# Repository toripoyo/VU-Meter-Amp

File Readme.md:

VU Meter Driver Amp

* -10dBv/+4dBm input level select
* 0 to -15dB 6step gain select
* Meter brightness adjust

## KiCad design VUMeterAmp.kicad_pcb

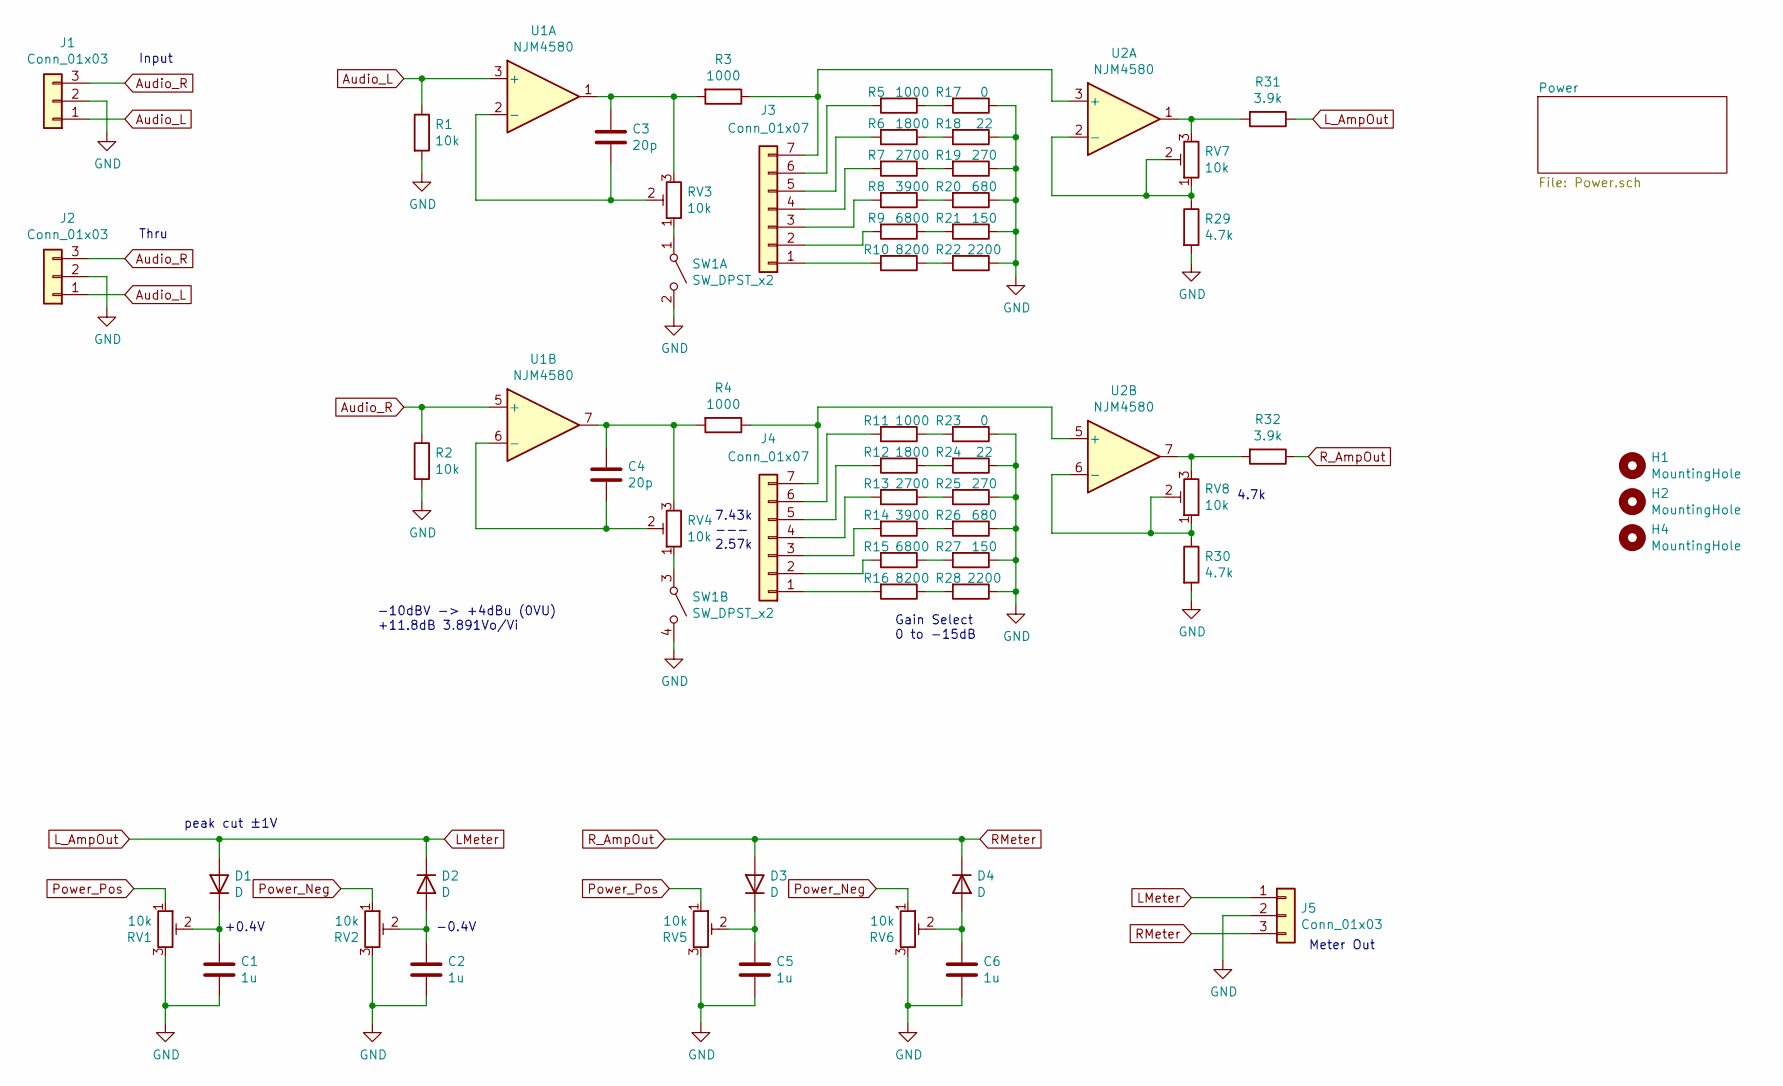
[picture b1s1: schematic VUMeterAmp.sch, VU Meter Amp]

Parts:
C1, C2, C5, C6: 1u; C_0603_1608Metric_Pad1.05x0.95mm_HandSolder
C3, C4: 20p; C_0603_1608Metric_Pad1.05x0.95mm_HandSolder
D1, D2, D3, D4: D; D_SOD-123F
H1, H2, H4: MountingHole; MountingHole_3.2mm_M3
J1, J2, J5: Conn_01x03; JST_XH_B3B-XH-A_1x03_P2.50mm_Vertical
J3, J4: Conn_01x07; JST_XH_B7B-XH-A_1x07_P2.50mm_Vertical
R1, R2: 10k; R_0603_1608Metric_Pad1.05x0.95mm_HandSolder
R3, R4, R5, R11: 1000; R_0603_1608Metric_Pad1.05x0.95mm_HandSolder
R6, R12: 1800; R_0603_1608Metric_Pad1.05x0.95mm_HandSolder
R7, R13: 2700; R_0603_1608Metric_Pad1.05x0.95mm_HandSolder
R8, R14: 3900; R_0603_1608Metric_Pad1.05x0.95mm_HandSolder
R9, R15: 6800; R_0603_1608Metric_Pad1.05x0.95mm_HandSolder
R10, R16: 8200; R_0603_1608Metric_Pad1.05x0.95mm_HandSolder
R17, R23: 0; R_0603_1608Metric_Pad1.05x0.95mm_HandSolder
R18, R24: 22; R_0603_1608Metric_Pad1.05x0.95mm_HandSolder
R19, R25: 270; R_0603_1608Metric_Pad1.05x0.95mm_HandSolder
R20, R26: 680; R_0603_1608Metric_Pad1.05x0.95mm_HandSolder
R21, R27: 150; R_0603_1608Metric_Pad1.05x0.95mm_HandSolder
R22, R28: 2200; R_0603_1608Metric_Pad1.05x0.95mm_HandSolder
R29, R30: 4.7k; R_0603_1608Metric_Pad1.05x0.95mm_HandSolder
R31, R32: 3.9k; R_0603_1608Metric_Pad1.05x0.95mm_HandSolder
RV1, RV2, RV3, RV4, RV5, RV6, RV7, RV8: 10k; Potentiometer_Bourns_3296W_Vertical
SW1: SW_DPST_x2; JST_XH_B4B-XH-A_1x04_P2.50mm_Vertical
U1, U2: NJM4580; SO-8_3.9x4.9mm_P1.27mm

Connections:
Audio_L: J1.1, J2.1, R1.1, U1.3 (+)
Audio_R: J1.3, J2.3, R2.1, U1.5 (+)
GND: C1.2, C2.2, C5.2, C6.2, J1.2, J2.2, J5.2, R1.2, R2.2, R17.1, R18.1, R19.1, R20.1, R21.1, R22.1, R23.1, R24.1, R25.1, R26.1, R27.1, R28.1, R29.2, R30.2, RV1.3, RV2.3, RV5.3, RV6.3, SW1.2 (B), SW1.4 (B); also elsewhere on the board
LMeter: D1.2 (A), D2.1 (K), J5.1, R31.1
unnamed: C1.1, D1.1 (K), RV1.2
unnamed: C2.1, D2.2 (A), RV2.2
unnamed: C3.1, R3.2, RV3.3, U1.1
unnamed: C3.2, RV3.2, U1.2 (-)
unnamed: C4.1, R4.2, RV4.3, U1.7
unnamed: C4.2, RV4.2, U1.6 (-)
unnamed: C5.1, D3.1 (K), RV5.2
unnamed: C6.1, D4.2 (A), RV6.2
unnamed: J3.1, R10.2
unnamed: J3.2, R9.2
unnamed: J3.3, R8.2
unnamed: J3.4, R7.2
unnamed: J3.5, R6.2
unnamed: J3.6, R5.2
unnamed: J3.7, R3.1, U2.3 (+)
unnamed: J4.1, R16.2
unnamed: J4.2, R15.2
unnamed: J4.3, R14.2
unnamed: J4.4, R13.2
unnamed: J4.5, R12.2
unnamed: J4.6, R11.2
unnamed: J4.7, R4.1, U2.5 (+)
unnamed: R10.1, R22.2
unnamed: R11.1, R23.2
unnamed: R12.1, R24.2
unnamed: R13.1, R25.2
unnamed: R14.1, R26.2
unnamed: R15.1, R27.2
unnamed: R16.1, R28.2
unnamed: R5.1, R17.2
unnamed: R6.1, R18.2
unnamed: R7.1, R19.2
unnamed: R8.1, R20.2
unnamed: R9.1, R21.2
unnamed: R29.1, RV7.1, RV7.2, U2.2 (-)
unnamed: R30.1, RV8.1, RV8.2, U2.6 (-)
unnamed: R31.2, RV7.3, U2.1
unnamed: R32.2, RV8.3, U2.7
unnamed: RV3.1, SW1.1 (A)
unnamed: RV4.1, SW1.3 (A)
Power_Neg: RV2.1, RV6.1; also elsewhere on the board
Power_Pos: RV1.1, RV5.1; also elsewhere on the board
RMeter: D3.2 (A), D4.1 (K), J5.3, R32.1

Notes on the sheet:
-10dBV -> +4dBu (0VU) +11.8dB 3.891Vo/Vi
Input
Thru
Gain Select 0 to -15dB
Meter Out
7.43k --- 2.57k
4.7k
peak cut ±1V
+0.4V
-0.4V

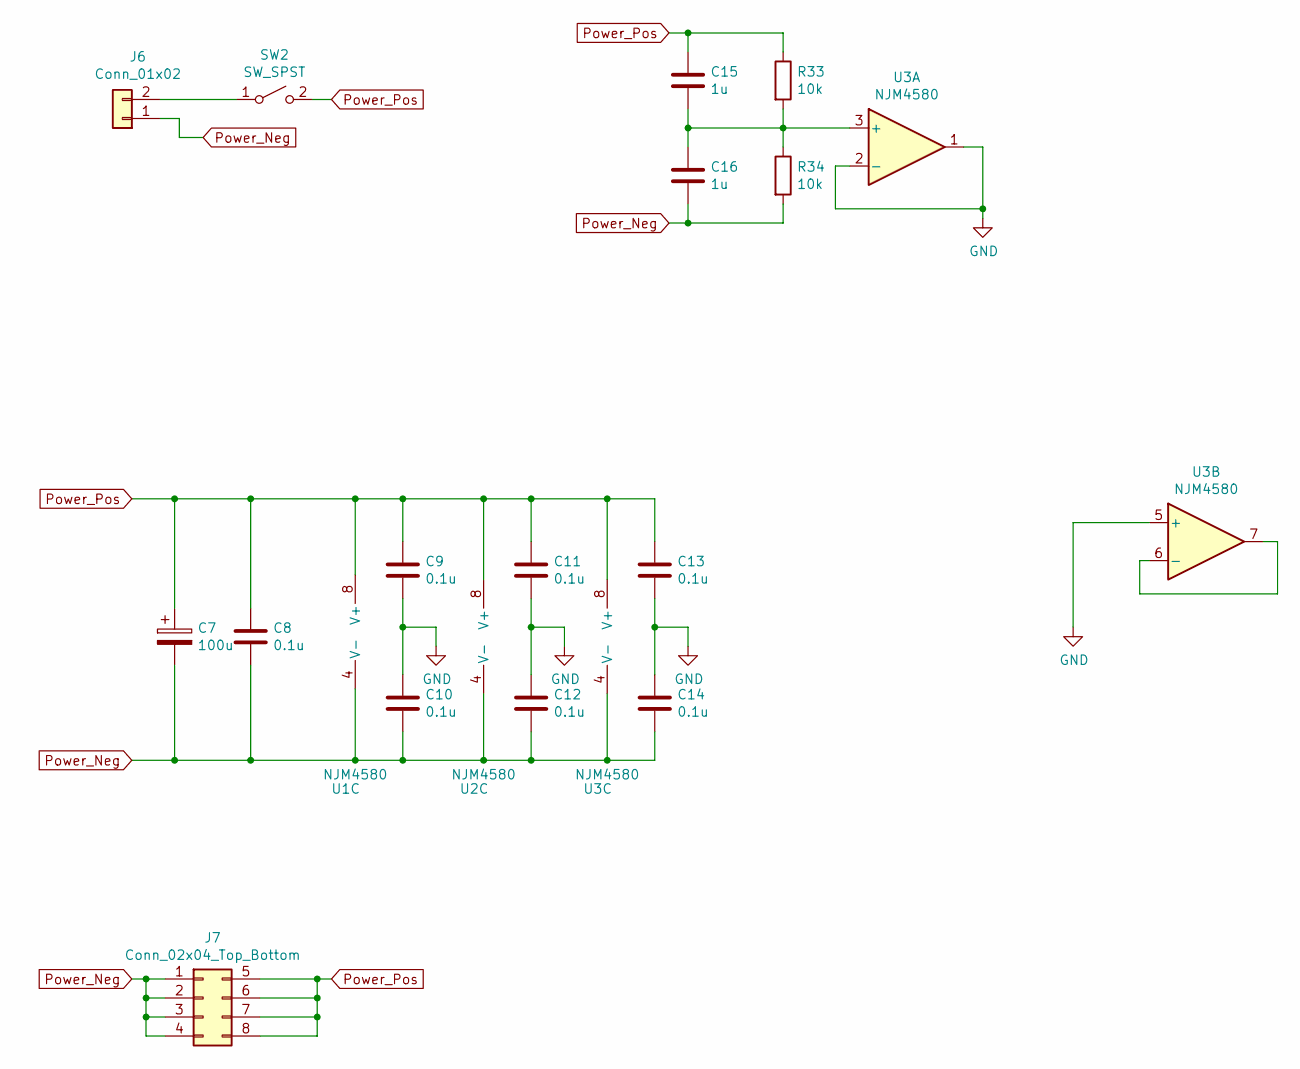
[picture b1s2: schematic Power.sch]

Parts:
C7: 100u; CP_Radial_D6.3mm_P2.50mm
C8, C9, C10, C11, C12, C13, C14: 0.1u; C_0603_1608Metric_Pad1.05x0.95mm_HandSolder
C15, C16: 1u; C_0603_1608Metric_Pad1.05x0.95mm_HandSolder
J6: Conn_01x02; JST_XH_B2B-XH-A_1x02_P2.50mm_Vertical
J7: Conn_02x04_Top_Bottom; PinSocket_2x04_P2.54mm_Vertical
R33, R34: 10k; R_0603_1608Metric_Pad1.05x0.95mm_HandSolder
SW2: SW_SPST; JST_XH_B2B-XH-A_1x02_P2.50mm_Vertical
U1, U2, U3: NJM4580; SO-8_3.9x4.9mm_P1.27mm

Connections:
GND: C9.2, C10.1, C11.2, C12.1, C13.2, C14.1, U3.1, U3.2 (-), U3.5 (+); also elsewhere on the board
unnamed: C15.2, C16.1, R33.2, R34.1, U3.3 (+)
unnamed: J6.2, SW2.1 (A)
unnamed: U3.6 (-), U3.7
Power_Neg: C7.2, C8.2, C10.2, C12.2, C14.2, C16.2, J6.1, J7.1, J7.2, J7.3, J7.4, R34.2, U1.4 (V-), U2.4 (V-), U3.4 (V-); also elsewhere on the board
Power_Pos: C7.1, C8.1, C9.1, C11.1, C13.1, C15.1, J7.5, J7.6, J7.7, J7.8, R33.1, SW2.2 (B), U1.8 (V+), U2.8 (V+), U3.8 (V+); also elsewhere on the board

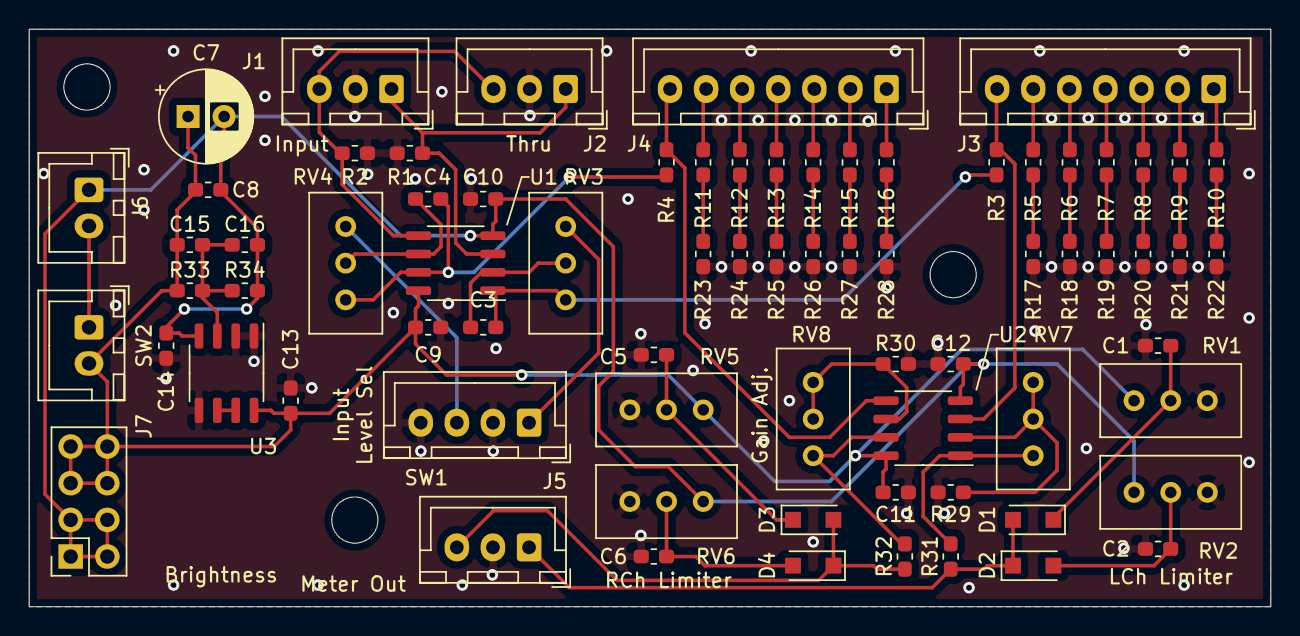
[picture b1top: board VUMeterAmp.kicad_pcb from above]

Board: 2 copper layers, 86.0 x 40.0 mm, 77 parts (0 on the bottom side), 50 nets.

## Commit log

2020-12-27 add gbr
